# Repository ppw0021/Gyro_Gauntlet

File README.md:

# Gyro Mouse

This is an Arduino powered device that wireless connects to a computer via a RF module. You can control the computer as if you had an invisible mouse in your hand using hand gestures and motions.

## Description

The Gyro Mouse is a wrist mounted arduino-powered device that uses RF modules to communicate with another arduino and interpreted and translated into mouse movements using a Python script.
Standard gestures:
- By clicking your left finger, you left click.
- By clicking your middle finger you right click.
- By clicking your ring finger, you re-centre the mouse.
- When clicking left and right at the same time, the mouse is locked in place, and any movements made by the mouse are translated into scrolling motion instead of mouse movements.

## 3D printed parts and CNC machined parts
The frame of the gyro mouse is 3D printed and modeled to fit onto the right hand of an individual. The finger rings are also 3D printed and bend slightly to allow for clicking gestures.

Frame:

I designed the frame using Fusion 360.
I recommend using Black, White and Clear PLA or ABS plastic at 0.1mm layer height for best results. 

The PCB board was designed using DipTrace and machined using a CNC machine.

Based on this schematic I created:

Drilled PCB:

## Electronics

This project has 2 seperate microcontrollers. One that connects to the computer and one that is on board the gyro-glove itself. 
Gyro-Glove components:
- 3x button switches
- 1x Arduino Nano
- 1x MPU6050 gyroscope module
- 3x 1k ohm resistors (pulldown)
- 1x 9V battery and battery holder
- 1x power switch
- 1x NRF24L01 Radio module

Receiver module components
- 1x Arduino uno
- 1x NRF24L01 Radio module

## Prerequisites

The following libraries are required:
pip install mouse
pip install pyserial 
or 
pip3 install mouse
pip install pyserial
pip install tkinter

## Code

There is three programs that are needed for the Gyro-Gauntlet to work. The first program (transmitter.ino) is loaded onto the Arduino Nano onboard the gyro-glove, this code translates the readings from the Gyroscope module into numbers (as well as the states of the switches) and transmits it to the reciever module which has the second program loaded (reciever.ino). This code processes the recieved transmission and transmitts it via serial to the third and final code, the python script (MouseController.py) that inteprets the numbers and states of the switches and converts the raw rotation numbers and switch positions into moues movements. There is also an additional file named Arduino.py that acts as a function library for MouseController.py.

transmitter.ino
```cpp
/*
   Written by Declan Ross
   Wireless mouse transmitter
*/
//Include Libraries
#include <SPI.h>
#include <nRF24L01.h>
#include <RF24.h>
#include <Wire.h>
#include <MPU6050.h>

MPU6050 mpu;

// Pitch, Roll and Yaw values
float pitch = 0;
float roll = 0;
float yaw = 0;
float timeStep = 0.01;

//Codes used to verify to the python script that the data entry code was recieved correctly
char pythonSendVerifCode = '5';
char pythonReadVerifCode = '8';

int LeftMouseClick = 5;
String LeftMouseState = "f";

int CenterButton = 2;
String CenterButtonState = "f";

int RightMouseClick = 4;
String RightMouseState = "f";

//create an RF24 object
RF24 radio(9, 8);  // CE, CSN

//address through which two modules communicate.
const byte address[6] = "00001";

const bool TEST = false;

void setup() {
  //Button state declaration
  pinMode(LeftMouseClick, INPUT);
  pinMode(CenterButton, INPUT);
  pinMode(RightMouseClick, INPUT);

  while (!mpu.begin(MPU6050_SCALE_2000DPS, MPU6050_RANGE_2G)) {
    //Serial.println("Could not find a valid MPU6050 sensor, check wiring!");
    delay(500);
  }

  // Calibrate gyroscope. The calibration must be at rest.
  // If you don't want calibrate, comment this line.
  mpu.calibrateGyro();

  // Set threshold sensivty. Default 3.
  // If you don't want use threshold, comment this line or set 0.
  mpu.setThreshold(3);

  if (TEST) {
    Serial.begin(115200);
  }
  radio.begin();
  //set the address
  radio.openWritingPipe(address);
  //Set module as transmitter
  radio.stopListening();
  radio.setRetries(0, 0);
}

void loop() {
  unsigned long currentTime = millis();
  static unsigned long previousTime = 0;
  static unsigned long interval = 1;
  while (currentTime - previousTime >= interval) {
    previousTime = currentTime;
  }

  // Read normalized values
  Vector norm = mpu.readNormalizeGyro();
  // Calculate Pitch, Roll and Yaw
  pitch = pitch + norm.YAxis * timeStep;
  roll = roll + norm.XAxis * timeStep;
  yaw = yaw + norm.ZAxis * timeStep;
  
  //Send message to receiver

  String dataType = "A";
  String yawVal = String(yaw);
  String pitchVal = String(pitch);
  String rollVal = String(roll);
  if (digitalRead(LeftMouseClick) == HIGH) {
    LeftMouseState = "t";
  } else {
    LeftMouseState = "f";
  }
  if (digitalRead(CenterButton) == HIGH) {
    CenterButtonState = "t";
  } else {
    CenterButtonState = "f";
  }
  if (digitalRead(RightMouseClick) == HIGH) {
    RightMouseState = "t";
  } else {
    RightMouseState = "f";
  }
  //String dataToWrite = "A:0.00:0.00:T:T";
  String dataToWrite = String(dataType + ":" + rollVal + ":" + yawVal + ":" + LeftMouseState + ":" + RightMouseState + ":" + CenterButtonState + ":" + pitchVal + ":" + "0");
  int dataLength = dataToWrite.length();
  char i[dataLength];

  dataToWrite.toCharArray(i, dataLength);

  radio.write(&i, sizeof(i));
  if (TEST) {
    Serial.println(i);
  }
}

```

reciever.ino
```cpp
//Include Libraries
#include <SPI.h>
#include <RF24.h>

//create an RF24 object
RF24 radio(9, 8);  // CE, CSN

//address through which two modules communicate.
const byte address[6] = "00001";

char text[32] = {0};

char pythonSendVerifCode = '5';
char pythonReadVerifCode = '8';

bool TEST = false;

void setup()
{
  while (!Serial);
  Serial.begin(115200);

  radio.begin();

  //set the address
  radio.openReadingPipe(0, address);

  //Set module as receiver
  radio.startListening();
}

void loop()
{
  //Read the data if available in buffer
  if (radio.available())
  {
    //Serial.println("Read");
    radio.read(&text, sizeof(text));
    
  }
  if (TEST)
    {
      String dataToWrite = text;
      Serial.print(dataToWrite);
      Serial.write("\n");
    }
  if (Serial.available() > 0)
  {
    //Store the read data as a CHAR, this is an indicator to what the controller wants (Lowercase means UPDATE FROM python, uppercase means to UPDATE python)
    char dataRecieved = Serial.read();
    //Example of UPDATE FROM python if statement
    if (dataRecieved == 'r')
    {
      //Handshake byte to confirm arduino is ready to recieve
      Serial.write(pythonSendVerifCode);
      //Wait until python sends back a value
      while (!Serial.available()) {}
      //Read the value
      char Val = Serial.read();
      //Update the independent function
    }

    if (dataRecieved == 'I') {
      Serial.write(pythonReadVerifCode);
      Serial.write("1\n");
      TEST = true;
    }
    if (dataRecieved == 'A') {
      String dataToWrite = text;
      Serial.print(dataToWrite);
      Serial.write("\n");
    }
    else {}
  }
  unsigned long currentTime = millis();
  static unsigned long previousTime = 0;
  static unsigned long interval = 1;
  while (currentTime - previousTime >= interval) {
    previousTime = currentTime;
  }
}

```

Arduino.py
```python
# Written by Declan Ross
# Serial MASTER connection with Arduino

#To download Serial
#https://www.instructables.com/id/How-to-Communicate-With-Arduino-From-a-Python-Scri/
#https://pyserial.readthedocs.io/en/latest/pyserial.html
import serial

#This checks if the byte recieved is correct
verificationSendCode = b'5'
verificationRecieveCode = b'8'

checkVerifOnRead = False

def getPos(serialData):
    return serialData.readline();

def communicate(serialData, requesting, data, val):
    if (requesting == False):
        serialData.write(data.encode())
        checkVerification = serialData.read()
        if (checkVerification != verificationSendCode):
            print("Arduino Handshake failed")
            return
        else:
            print("Arduino Handshake succeeded")
            serialData.write(chr(val).encode())
            #Value as char
            #print(chr(val))
            return
    if (requesting == True):
        serialData.write(data.encode())
        if checkVerifOnRead == True:
            checkVerification = serialData.read()
            if (checkVerification != verificationRecieveCode):
                print("Arduino Handshake failed")
                return
            else:
                print("Arduino Handshake succeeded")
                rawData = serialData.readline()
                return rawData
        else:
            rawData = serialData.readline()
            return rawData            

def connect(serialData, data, val):
    if (1 == 1):
        serialData.write(data.encode())
        checkVerification = serialData.read()
        if (checkVerification != verificationRecieveCode):
            return
        else:
            print("Arduino Handshake succeeded")
            rawData = serialData.readline()
            if (float(rawData) == 1.0):
                return True
            else:
                return False
#def sendRequest(variableData, data):
    #variableData.write(data.encode())
    #x=variableData.readline()
    #y=variableData.readline()
    #z=variableData.readline()
    #print(x, y, z)   
    #return

#Arduino value is not being flushed correctly :///
#def sendShutDown(variableData):
    #variableData.write('y'.encode())
    #print(variableData.readline())
    #return

```

MouseController.py
```python
#pip install mouse
#pip install pyserial
#or pip3 install mouse
import mouse

import Arduino
import time
import serial
from tkinter import *

#Resolution
ScreenHeight = 1440
ScreenLength = 2560

#Screen center
HeightStartPos = (ScreenHeight/2)
LengthStartPos = (ScreenLength/2)

#Sensitivity
HeightSens = 16
LengthSens = 16
scrollSens = 0.5

#Offset from center for calibration
HeightOffset = 0
LengthOffset = 0

leftHeldDown = False
rightHeldDown = False

moveMouse = True
mouseScrolling = False

currentTime = 0

last = 0
startTime = time.time()

ser1 = serial.Serial("COM3", 115200, timeout=0.05)
def tryConnect():
    data = 'I'
    return Arduino.connect(ser1, data, 0)

def requestGyroPos(data):
    stringVal = Arduino.communicate(ser1, True, data, 0)
    return (stringVal.decode("utf-8")).strip()

def requestAll():
    #stringVal = Arduino.communicate(ser1, True, 'A', 0)

    stringVal = Arduino.getPos(ser1);
    print(stringVal)
    stringVal = stringVal.decode("utf-8")
    X = stringVal.split(":")
    return X

for x in range(300):
    connectionEstablished = False
    print("Connecting...")
    if connectionEstablished == False:
        y = tryConnect()
    if (y == True):
        connectionEstablished = True
        print("Connection established")
        break
    if (x == 299) and (connectionEstablished == False):
        print("Connection failed")

while(True):
    #Use for 60HZ
    #time.sleep(0.010);
    #time.sleep(0.016)
    #Use for 144HZ
    #time.sleep(0.00694)
    try:
        AllDataList = requestAll()
    except:
        continue
    #print(AllDataList)
    if (AllDataList[0] == "A"):
	#x = float(AllDataList[1].strip())
        #y = float(AllDataList[2].strip())

	#Reversed
        y = 0 - float(AllDataList[1].strip())
        x = float(AllDataList[2].strip())
        subfinalx = LengthStartPos - ((LengthSens * x) - LengthOffset)
        subfinaly = HeightStartPos - ((HeightSens * y) - HeightOffset)
        finalx = float(subfinalx)
        finaly = float(subfinaly)
        #print((finalx, finaly))
        if (AllDataList[3] == 't'):
            if mouseScrolling == False:
                if leftHeldDown == False:
                    mouse.press(button='left')	
                    leftHeldDown = True            
            if (AllDataList[4] == 't'):
                mouseScrolling = True
                moveMouse = False
                if (currentTime == 0):
                    currentTime = time.time()
                val = time.time() - currentTime
                if (val) > 0.00694:
                    currentTime = time.time()
                    difference = subfinalx - last
                    moveAmount = (difference * scrollSens)/-5
                    mouse.wheel(delta=(moveAmount))
                    last = finalx
                mouse.release(button="left")

        if (AllDataList[5] == 't'):
            LengthOffset = (LengthSens * x)
            HeightOffset = (HeightSens * y)
        if (AllDataList[4] == 't'):
            if (rightHeldDown == False):
                if (mouseScrolling == False):
                    moveMouse = True
                    mouse.click(button='right')
                    rightHeldDown = True
        if (AllDataList[3] == 'f'):
            if mouseScrolling == False:
                moveMouse = True
                mouse.release(button='left')
                leftHeldDown = False           
        else:
            mouseScrolling = False	
            rightHeldDown = False 
        if (moveMouse == True):
            mouse.move(finalx, finaly, absolute=True, duration=0)

```

## Version History

* 1.0
    * Initial Release

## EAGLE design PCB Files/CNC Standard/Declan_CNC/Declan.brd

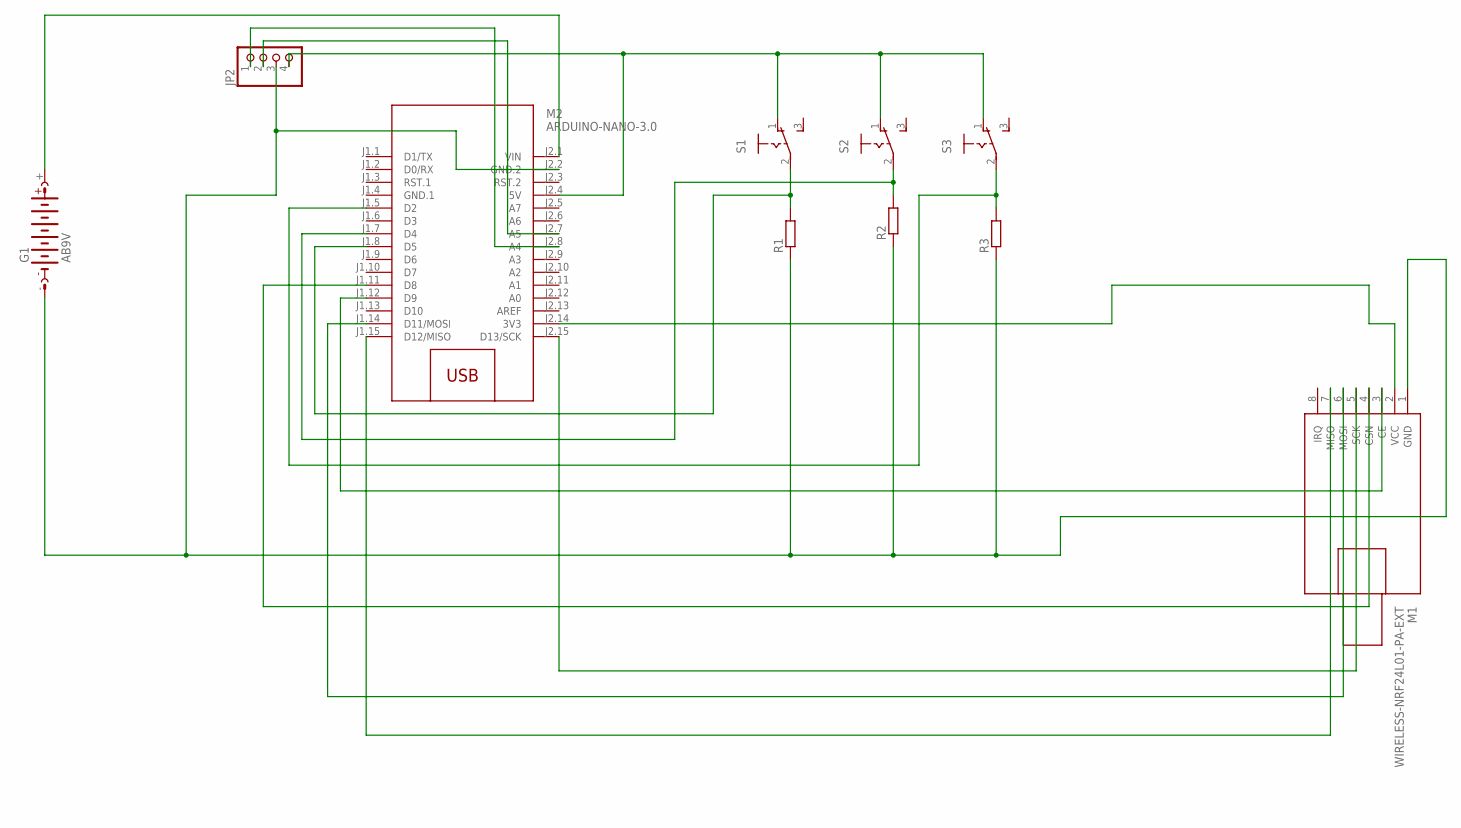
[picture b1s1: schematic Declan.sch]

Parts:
G1: AB9V
JP2: PINHD-1X4; 1X04
M1: WIRELESS-NRF24L01-PA-EXT
M2: ARDUINO-NANO-3.0
R1, R2, R3: R-EU_0207/10; 0207/10
S1, S2, S3: 255SB

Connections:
GND.1: M2.J1.4 (GND.1)
unnamed: JP2.2, M2.J2.7 (A5)
unnamed: JP2.1, M2.J2.8 (A4)
unnamed: G1.-, JP2.3, M1.1 (GND), M2.J2.2 (GND.2), R1.1, R2.1, R3.1
unnamed: JP2.4, M2.J2.4 (5V), S1.1 (O), S2.1 (O), S3.1 (O)
unnamed: M2.J1.8 (D5), R1.2, S1.2
unnamed: M2.J1.7 (D4), R2.2, S2.2
unnamed: M2.J1.5 (D2), R3.2, S3.2
unnamed: G1.+, M2.J2.1 (VIN)
unnamed: M1.2 (VCC), M2.J2.14 (3V3)
unnamed: M1.3 (CE), M2.J1.12 (D9)
unnamed: M1.4 (CSN), M2.J1.11 (D8)
unnamed: M1.5 (SCK), M2.J2.15 (D13/SCK)
unnamed: M1.6 (MOSI), M2.J1.14 (D11/MOSI)
unnamed: M1.7 (MISO), M2.J1.15 (D12/MISO)

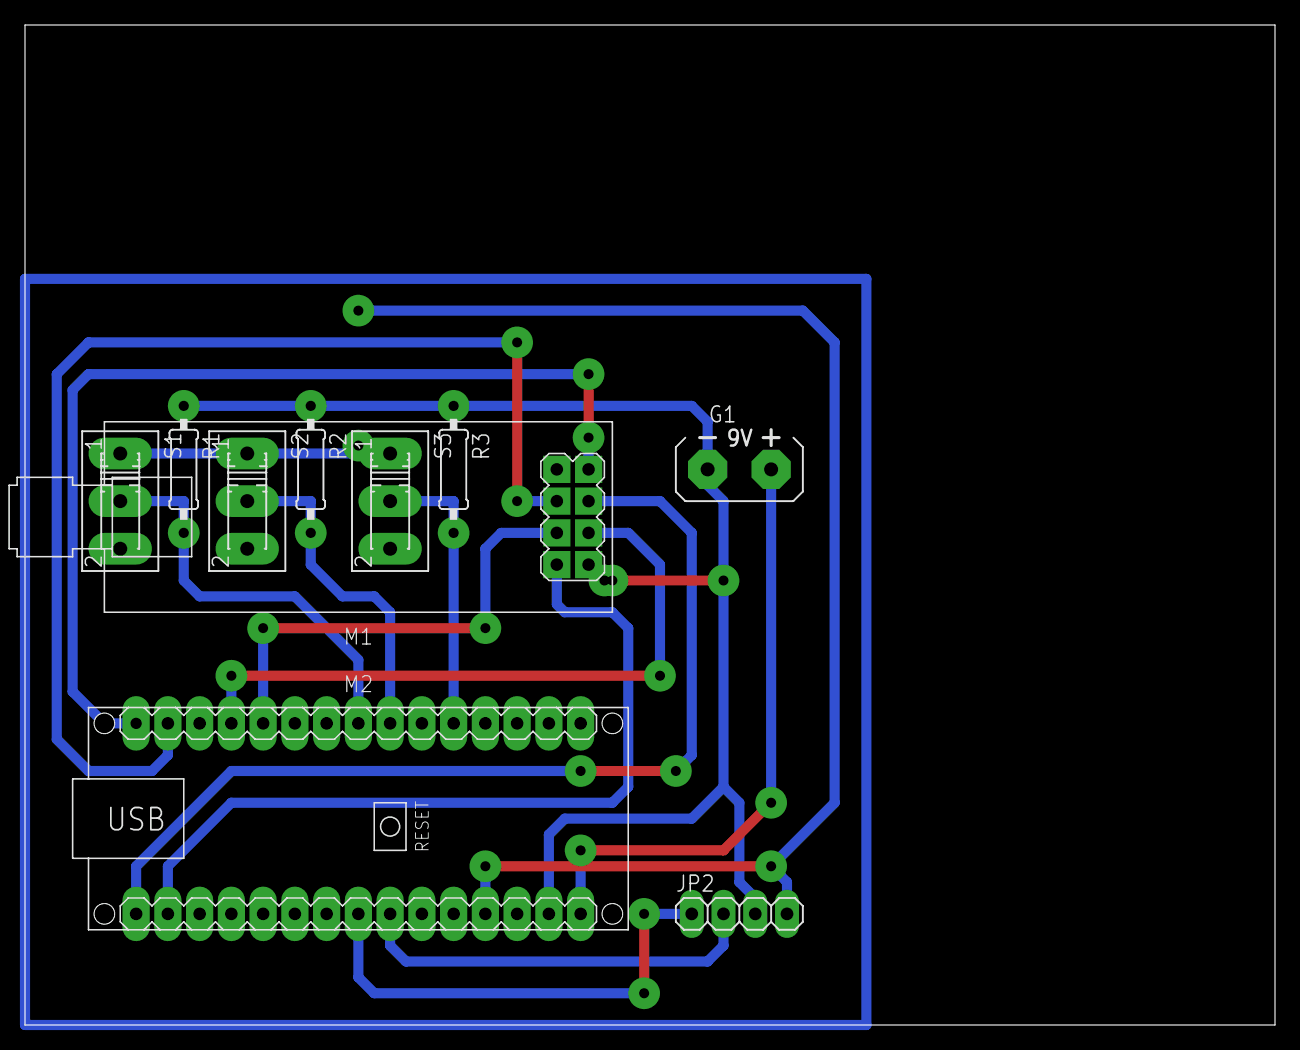
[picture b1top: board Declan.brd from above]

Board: 2 copper layers, 100.0 x 80.0 mm, 10 parts (0 on the bottom side), 14 nets.

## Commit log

2024-01-05 Files added
2024-01-05 Added 3D files
2024-01-06 Found working code
    Changed from polling to viewing
2024-02-06 Streamlined files names
2025-02-24 Updated code

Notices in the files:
parts and their libraries:
diy-modules: Released under the Creative Commons Attribution 4.0 International License: http://creativecommons.org/licenses/by/4.0
